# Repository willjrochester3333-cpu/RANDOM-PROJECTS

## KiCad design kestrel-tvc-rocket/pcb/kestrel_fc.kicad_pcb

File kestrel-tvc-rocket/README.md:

# KESTREL-2: a thrust-vector-controlled model rocket with four steerable fins

A reusable, 3D-printed, ~0.9 m model rocket that flies to about **157 m** on a TSP F35, **steers its motor**
(two-axis thrust vector control) and its
**four fin tabs** (roll, pitch and yaw; each tab's servo sits inside the thick bottom band of its fin and turns it
directly),
**stands up on its own four fins**, releases its parachute **at apogee**
with a servo latch under the nose cone (no pyrotechnics), carries a **payload of up to 50 g** behind a lockable
door, films the flight with a camera hidden inside it (looking out 30° down through a door with a lens port), logs
IMU, barometer and GPS data on a **custom flight-computer PCB** built around a Raspberry Pi Pico 2 W, and **sends
it all down live** over a licence-free 433 MHz telemetry radio (50 motion and 5 status frames a second) to
**Mission Control**, which flies the rocket on a 3D map as it happens and **predicts where it will land**. It
comes with its own launch pad. It is built to
**fly again and again**: the legs it stands and lands on are **replaceable** (one bolt each, and designed to be the
part that breaks after a hard landing, not the fin can), and a **battery hatch** with a gap-free door lets you swap
the LiPo and plug in USB between flights without taking anything apart. **No soldering
anywhere**: the PCB comes assembled from JLCPCB and everything else plugs, screws or glues together. Estimated
build cost **≈ £403–422** with the telemetry radio, ≈ £317 without it (motors extra).

**Simulated launch video** (ground camera, onboard camera, live telemetry bottom left, graphs below; every seed is a
different flight): [`kestrel2_flight_seed7.mp4`](sim/results/video/kestrel2_flight_seed7.mp4) (TSP F35, 4.9 m/s
wind, 20 g payload). Make another with `python3 sim/video/make_flight_video.py --seed N`.

**Mission Control** (the ground-station screen): a 3D map of the range with the rocket flying on it **live over the
radio**, the flight events as they happen (liftoff, burnout, apogee, parachute out, landed), telemetry, steering
dials and charts, the radio link's health, a **landing prediction** with a search ring and a position you can copy
to a phone map, and every flight saved for replay; after landing the full 500 Hz log comes in over USB and is merged
with the radio recording. Open [`ground/kestrel_mission_control.html`](ground/kestrel_mission_control.html) in Chrome
or Edge (one file, works offline); **Simulated live** shows a whole flight through a simulated radio link. See
[ground/README.md](ground/README.md).

| | |
|---|---|
| Parts | **3**: bottom (fin can + 4 replaceable legs + TVC module + camera behind its door + telemetry radio + flight computer + battery behind a hatch), middle (payload bay with door · wall · parachute bay · release latch at the top), nose cone |
| Length / diameter / fin span | 903 mm (929 mm standing on its fin feet) / 56.3 mm (Estes BT-70) / 159 mm |
| Lift-off mass | 952 g with a TSP F35 and 25 g of payload (861 g without motor) |
| Motors | 29 mm TSP **F35-0** (mission); 24 mm TSP **E20-0** for the first two flights, in a printed adapter sleeve (the D20 fits too, but is not in the flight programme) |
| Apogee (simulated, F35) | **157 m** nominal with 25 g of payload (164 m with an empty bay); Monte Carlo mean 166 m, 90 % of flights 135–200 m. E20: 41 m (about 47 m on the first flights, which carry no payload) |
| Stability | +0.72 to +0.84 calibres at lift-off (empty to full payload bay, with 51 g of nose ballast), +0.91 to +1.02 at burn-out: still flies straight enough to recover normally if all six steering servos fail |
| TVC | 2-axis gimbal for 29 mm motors, ±6° vector limit, 2 × MG90S, 500 Hz control loop |
| Fins | 4 × normal 4 mm fins with a half-round leading edge; only the bottom band (45 mm next to the tail) is 15 mm thick (17 mm round the servo), joined by a smooth 15° wedge, and holds the tab hinge, the tab servo (in a pocket open at the tip) and its lead channel; band and tabs taper to thin trailing edges below the tail |
| Multi-flight | **replaceable legs** (tough PLA, one M3 bolt onto a solid tongue under each fin tip; the post is the designed weak point at about 7.5 kg outward / 11.5 kg sideways at the foot, while the fin can holds about twice that); **battery hatch** on the rod side: the pack slides out and the Pico's USB socket is right there; the door sits on the tube and overlaps the opening by 2 mm all round |
| Fin tabs | 4 trailing-edge tabs, ±15°, each turned directly by an MG90S inside its fin (servo shaft = hinge line: no pods, pushrods or hinge pins); hold roll in boost and coast, share pitch/yaw with the TVC in the burn, steer alone in the coast |
| Recovery | 36 in parachute, spring ejection, servo-released snap-in latch, 5.2 m/s landing; from 157 m it drifts about 46 m for every 1 m/s of wind |
| Payload | 130 mm bay, 32 × 50 mm hinged door with a quarter-turn lock, 4 × M3 mounting holes, up to 50 g |
| Flight computer | Pico 2 W + LSM6DSO IMU + BMP580 baro + ATGM336H GPS + 16 MB log, 4-layer 40 × 82 mm PCB (v3), 7 servo ports, a radio socket |
| Telemetry | Holybro SiK V3 433 MHz pair, set to 8 dBm (≈ 6 mW e.r.p., inside the UK's 10 mW limit) and kept under the 10 %-an-hour airtime rule by the firmware; MAVLink-framed binary frames with a CRC, 50 motion + 5 status a second in flight, 1.5 a second on the pad. Nothing sent from the ground changes the flight: the rocket only notes the ground station's heartbeat |
| Camera | SQ12-class 23 mm cube **inside** the bottom tube, in a cradle behind a door with a lens port and a low brow, looking out 30° down (the old external pod is gone: −71 % camera drag) |
| Launch pad | printed hub, 3 dowel legs, 1 m (or 1.5 m) × 6 mm rod, 0–15° tilt, 200 mm tile the rocket stands on |

## How it was verified

- **Simulation with the real flight code in the loop.** A 6-DOF simulator, checked against RocketPy (every
  quantity within 0.3 %), flies the actual C++ flight software 500 times a second, including the fin-tab mixer.
  **Scenario and fault suite: 44 of 44 graded cases pass** (plus 3 informational cases).
  **1500-flight Monte Carlo** (1000 on the F35, 400 on the E20, 100 on the D20): **1500 of 1500** meet every
  normal-flight criterion. A **first-flight study** of the E20 (700 flights: flight 1 with the fin tabs off, flight
  2 with them on, and 100 in more wind than allowed): 700 of 700, the canopy fully open at about 40 m. A stress Monte
  Carlo with about twice the error spreads and wind up to 9 m/s: 99.7 % meet every normal-flight criterion and
  99.9 % recover safely; a tab-effectiveness Monte Carlo: 200 of 200. About 3,700 simulated flights on the final design.
  → [docs/SIMULATION_REPORT.md](docs/SIMULATION_REPORT.md)
- **CAD checked automatically on every run.** All 40 printed parts are watertight, single-body and fit a
  220 × 220 × 250 mm bed, and an overhang check confirms they print as exported without support material (three
  marked parts excepted). Exact-geometry interference checks cover 2485 part pairs, plus sweeps of every mechanism
  through its full travel: the gimbal in 24 directions at 7° (with the F35 and with the 24 mm adapter, against the
  frame, servos, horns and pushrods), all four tabs at ±17°, the payload door through 0–100° and the release latch.
  All come back clean. Masses and positions feed the simulator, the av-bay is
  generated from the PCB's KiCad layout, and every number the firmware and simulator take from `design.json`
  (linkage ratios, tab geometry, leg geometry, IMU position, the camera door's brow) is checked against the CAD. The
  strength of every section of the fin, leg and tongue is computed from slices of the real CAD solid.
- **PCB** (v3, with the radio socket): schematic checked pin-for-pin against the circuit source, DRC 0
  violations, all 65 nets routed, gerbers re-read by an independent viewer. → [docs/PCB.md](docs/PCB.md)
- **Firmware** (v3.00): 375,585 flight-core checks (including the radio frames against pymavlink's reference
  frames and an hour stuck at full rate against the airtime limit), 148 firmware-logic checks, a 0-warning
  cross-compile and a ready-to-flash UF2. → [docs/FIRMWARE.md](docs/FIRMWARE.md)
- **Mission Control**: its radio decoder is tested against pymavlink frames and against a second, independent
  decoder in Python, including a damaged link; the whole page was run in a headless browser through a simulated
  flight (55 frames a second, no errors).

Honest gaps against what we agreed:

- **Apogee**: you asked for 200 m. On the 29 mm TSP F35 the rocket reached 188 m; making it a multiple-flight
  rocket added 48 g (170 m), and the telemetry radio, its antenna and cradles and 5 g more nose ballast to keep the
  same stability added another 48 g, so it now reaches **157 m** with 25 g of payload (164 m with an empty bay).
  Hiding the camera inside cut its drag by 71 % and won back a little of that. The TVC module takes 29 mm motors;
  the E20 flies in a printed adapter for the first two flights. The price of height is drift: about 30 s under the
  parachute, so it needs a recovery area of about 500 m downwind in winds up to 6 m/s, or 250 m if you fly it only
  in 3 m/s or less. The details, with what-if numbers, are in the simulation report, section 3.
- **Budget**: ≈ £317 without the radio against the ~£270 we aimed for (four extra servos, the larger 36 in
  parachute, the ejection spring that only comes in a pack of 10, the servos-in-the-fins design and the multi-flight
  parts); the radio adds ≈ £86–105. Two radio items (the antenna and the antenna extension) were not price-checked.
  → [docs/BOM.md](docs/BOM.md)
- **Not checked on real hardware yet**: the radio's range inside the rocket (its antenna stands inside the
  airframe, next to the wiring), and the masses of the radio parts (estimates). The test plan has a bench and a
  field range test before the first flight.

**Where the project stands, in one page:** [docs/STATUS.md](docs/STATUS.md).

Real flights then confirm what models cannot; [docs/TEST_PLAN.md](docs/TEST_PLAN.md) takes you from the bench to
the first F35 flight in steps (two E20 flights first: TVC only, then with the fin tabs).

## Build it

1. **Order the PCB** (1–3 weeks): [docs/PCB.md → Ordering from JLCPCB](docs/PCB.md#ordering-from-jlcpcb)
2. **Buy the rest**: [docs/BOM.md](docs/BOM.md)
3. **Print and assemble**: [docs/BUILD_GUIDE.md](docs/BUILD_GUIDE.md)
4. **Flash and set up**: drag `firmware/pico/kestrel_fc.uf2` onto the Pico, then `calaxes`, `dirtest`, `tabtest`,
   `tvctest`, `fintest`
5. **Test**: [docs/TEST_PLAN.md](docs/TEST_PLAN.md) → **fly**: [docs/PREFLIGHT_CHECKLIST.md](docs/PREFLIGHT_CHECKLIST.md)
6. **Read first**: [docs/SAFETY_AND_LEGAL.md](docs/SAFETY_AND_LEGAL.md) (UKRA/BMFA, CAA, motors, LiPo, wind limits)

## What's where

Every file is listed and explained in [FILES.md](FILES.md).

```
design.json              master parameters: airframe, fins + tabs, TVC, payload, recovery, every component's mass/position
cad/                     Blender + manifold3d parametric model
  kestrel_cad.py           blender -b -P cad/kestrel_cad.py -- [--no-render] [--fast] [--view=NAME]
  kestrel.blend            scene 1: complete rocket + the same rocket cut open + every part laid out with its name;
                           scenes 2-7: exploded view, cut-aways, door open, tabs deflected, fin cut open, on the launch pad
  kestrel_rocket.blend     just the constructed rocket, every part in place; hide "Body tubes" to look inside
  kestrel_tvc_module.blend the TVC module on its own (its two servo leads come out of the top) + assembly steps
  kestrel_parachute_open.blend  the rocket descending under its open parachute
  stl/                     40 print-ready STLs + check_report.md (3 of them: the 24 mm motor adapter set)
  renders/                 the images above
  interference_report.md   part pairs and mechanism sweeps
pcb/                     KiCad 7 project, circuit-as-code, autorouter, production files for JLCPCB
  kestrel_fc.kicad_pro/.kicad_sch/.kicad_pcb, kestrel_fc_schematic.pdf
  production/              gerbers zip, BOM + pick-and-place CSVs, assembly drawing
firmware/
  core/                    flight core (estimation, TVC, fin-tab mixer, state machine) + unit tests
  pico/                    Pico 2 W application, drivers, host tests; kestrel_fc.uf2 = ready to flash
  sil/                     simulator bridge (software-in-the-loop)
  tools/                   kestrel_link.py (USB shell, log download, plots, radio recorder), gen_motor_db.py
sim/                     6-DOF simulator, scenarios, Monte Carlo, first-flight study, RocketPy validation, results/
  run_all.sh               every simulation suite in order (about 45 min on 4 cores)
  video/                   launch-video pipeline (simulation → Blender → telemetry + graphs → MP4)
docs/                    shopping list, build guide, PCB, firmware, test plan, checklist, safety, simulation report
ground/                  Mission Control: kestrel_mission_control.html = live radio, 3D map, landing prediction, replay (offline)
  radio_frames.py, test_radio.mjs   the radio frame format in Python + the page decoder's tests
```

## Change it

Everything is parametric and connected: edit `design.json` (or the PCB layout in `pcb/circuit.py`), then
re-run the chain. The CAD script stops with a message if `design.json` and the CAD/PCB disagree.

```bash
blender -b -P cad/kestrel_cad.py -- --no-render && python3 cad/check_parts.py && python3 cad/mass_properties.py
```

```bash
python3 firmware/tools/gen_motor_db.py && cmake --build firmware/build-host && (cd firmware/build-host && ctest)
```

```bash
sh sim/run_all.sh
```

Tools: Blender 4.0, KiCad 7, Python 3 (numpy, matplotlib, pillow, trimesh, manifold3d, rocketpy), ffmpeg,
Raspberry Pi Pico SDK 2.1, arm-none-eabi-gcc.

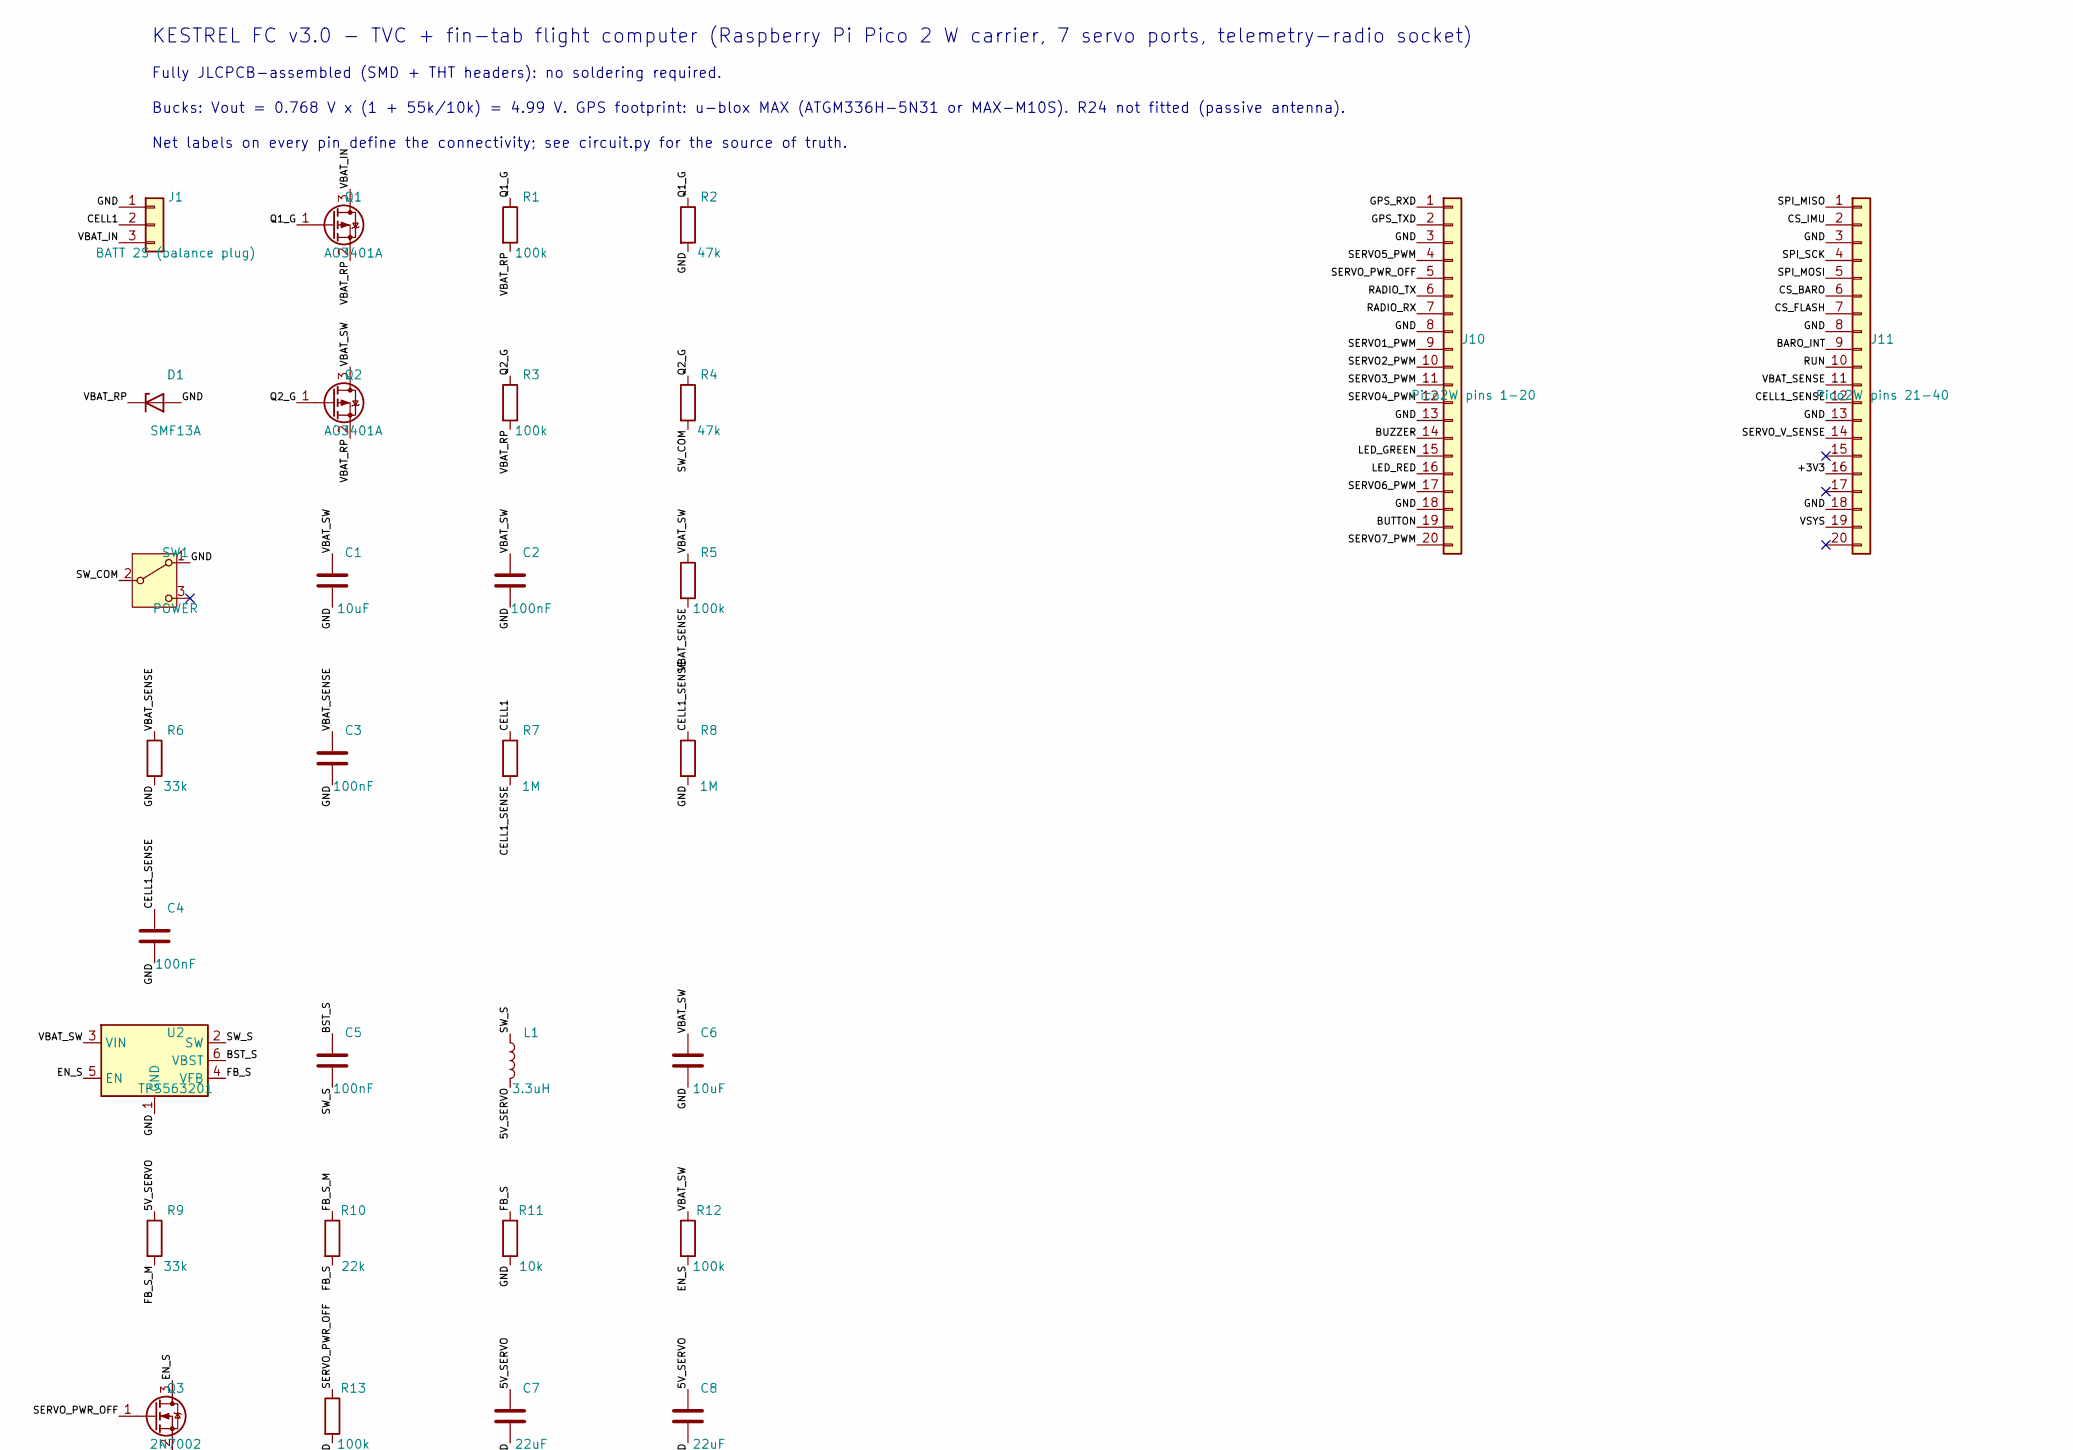
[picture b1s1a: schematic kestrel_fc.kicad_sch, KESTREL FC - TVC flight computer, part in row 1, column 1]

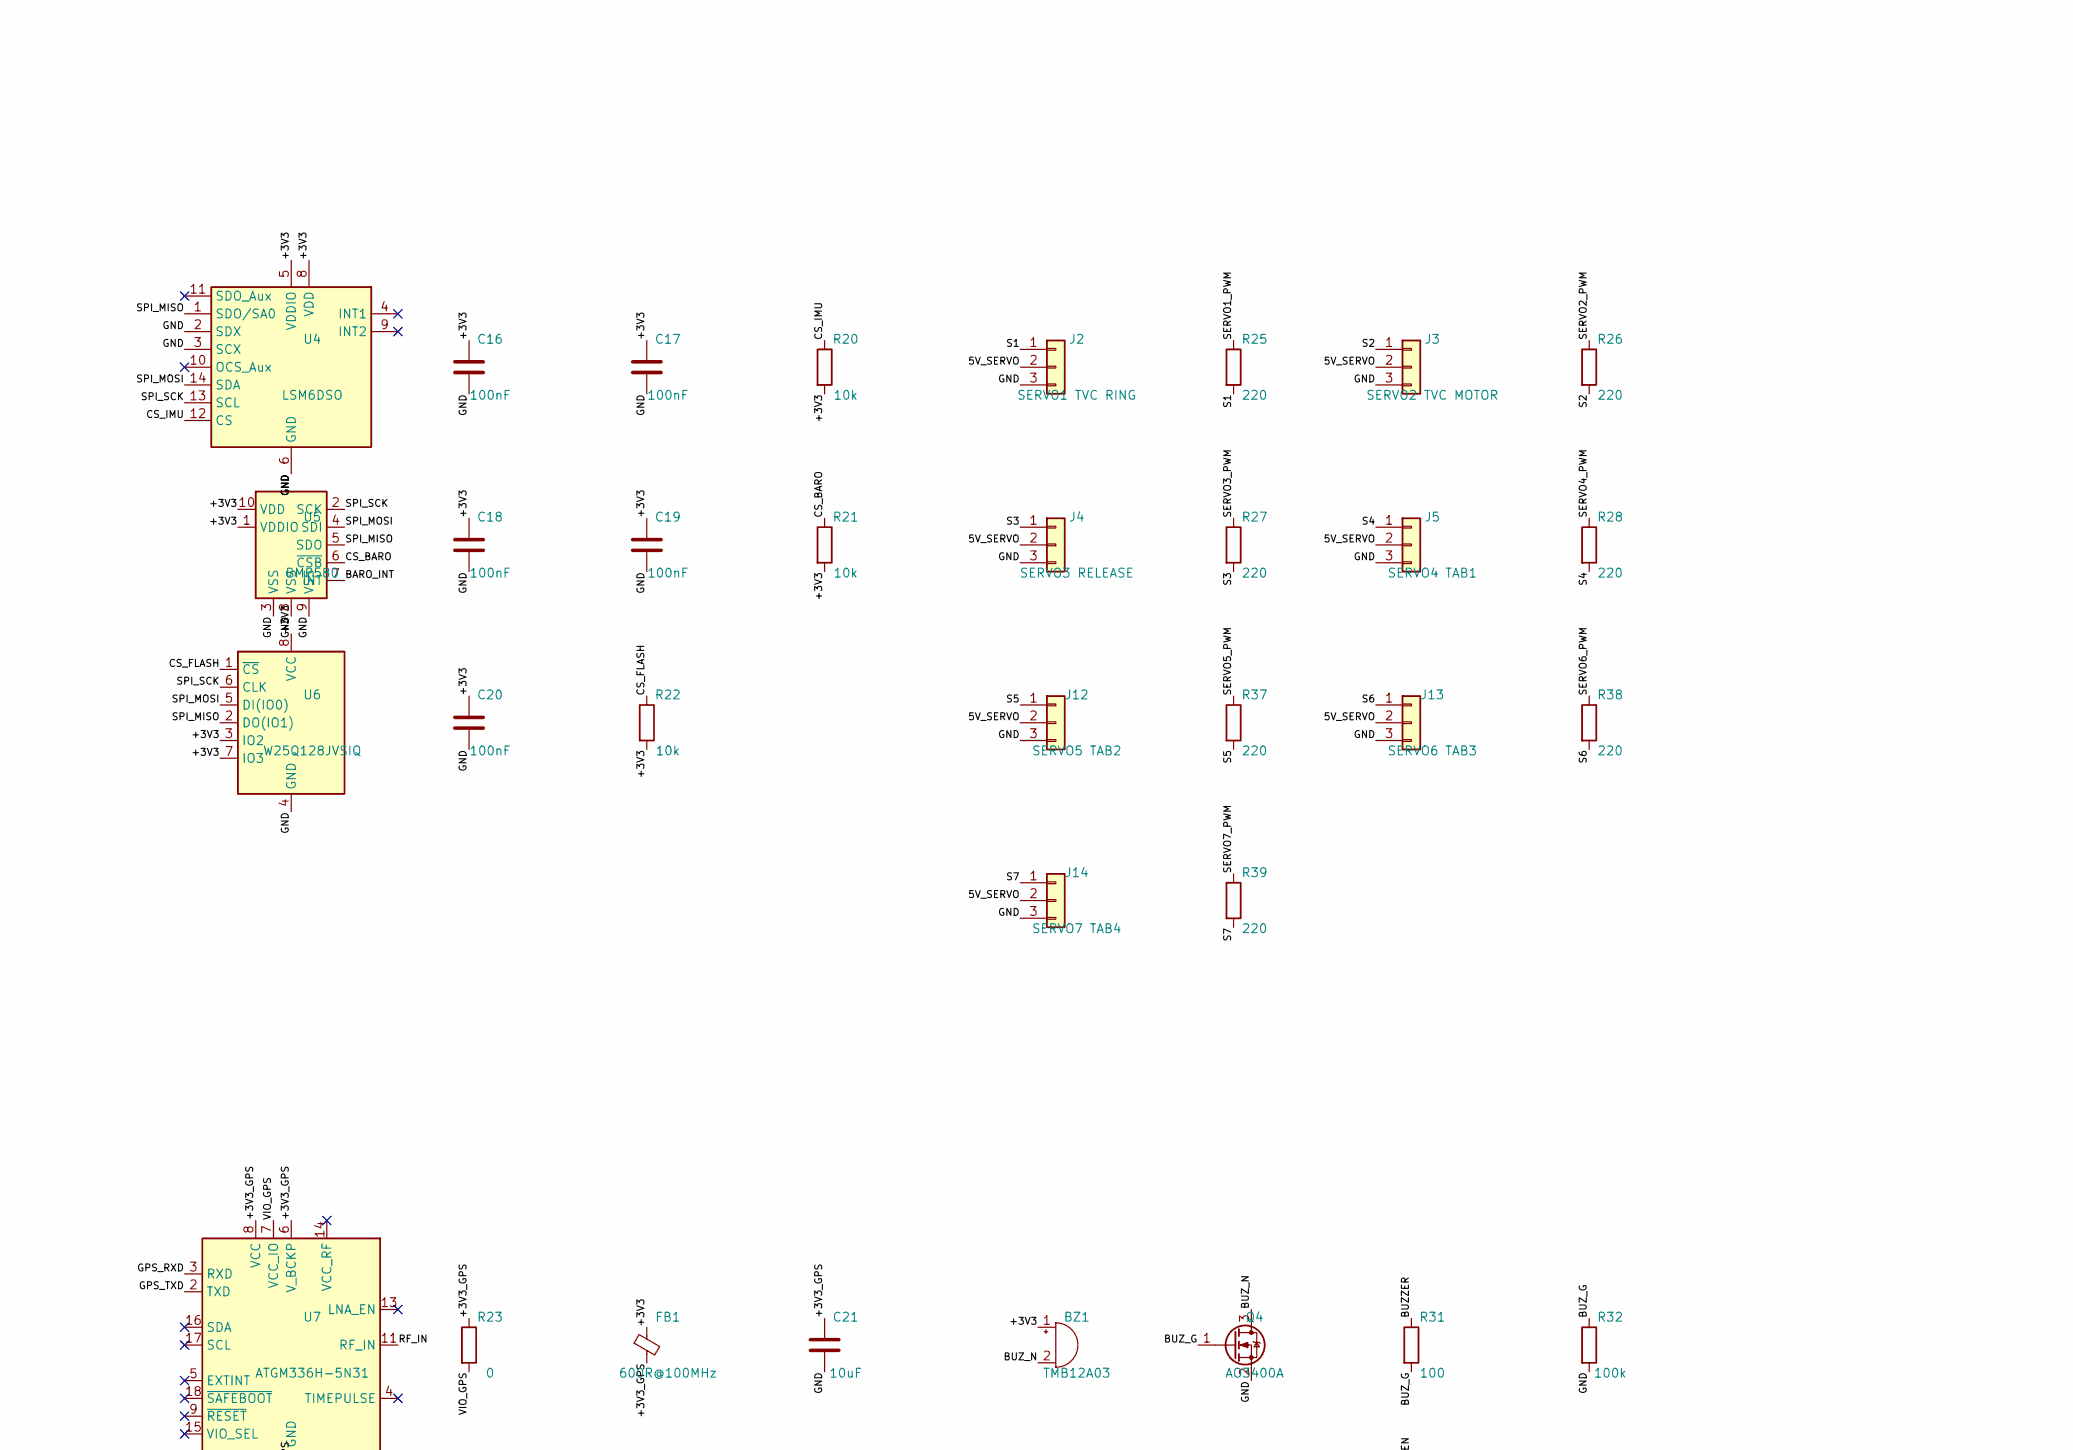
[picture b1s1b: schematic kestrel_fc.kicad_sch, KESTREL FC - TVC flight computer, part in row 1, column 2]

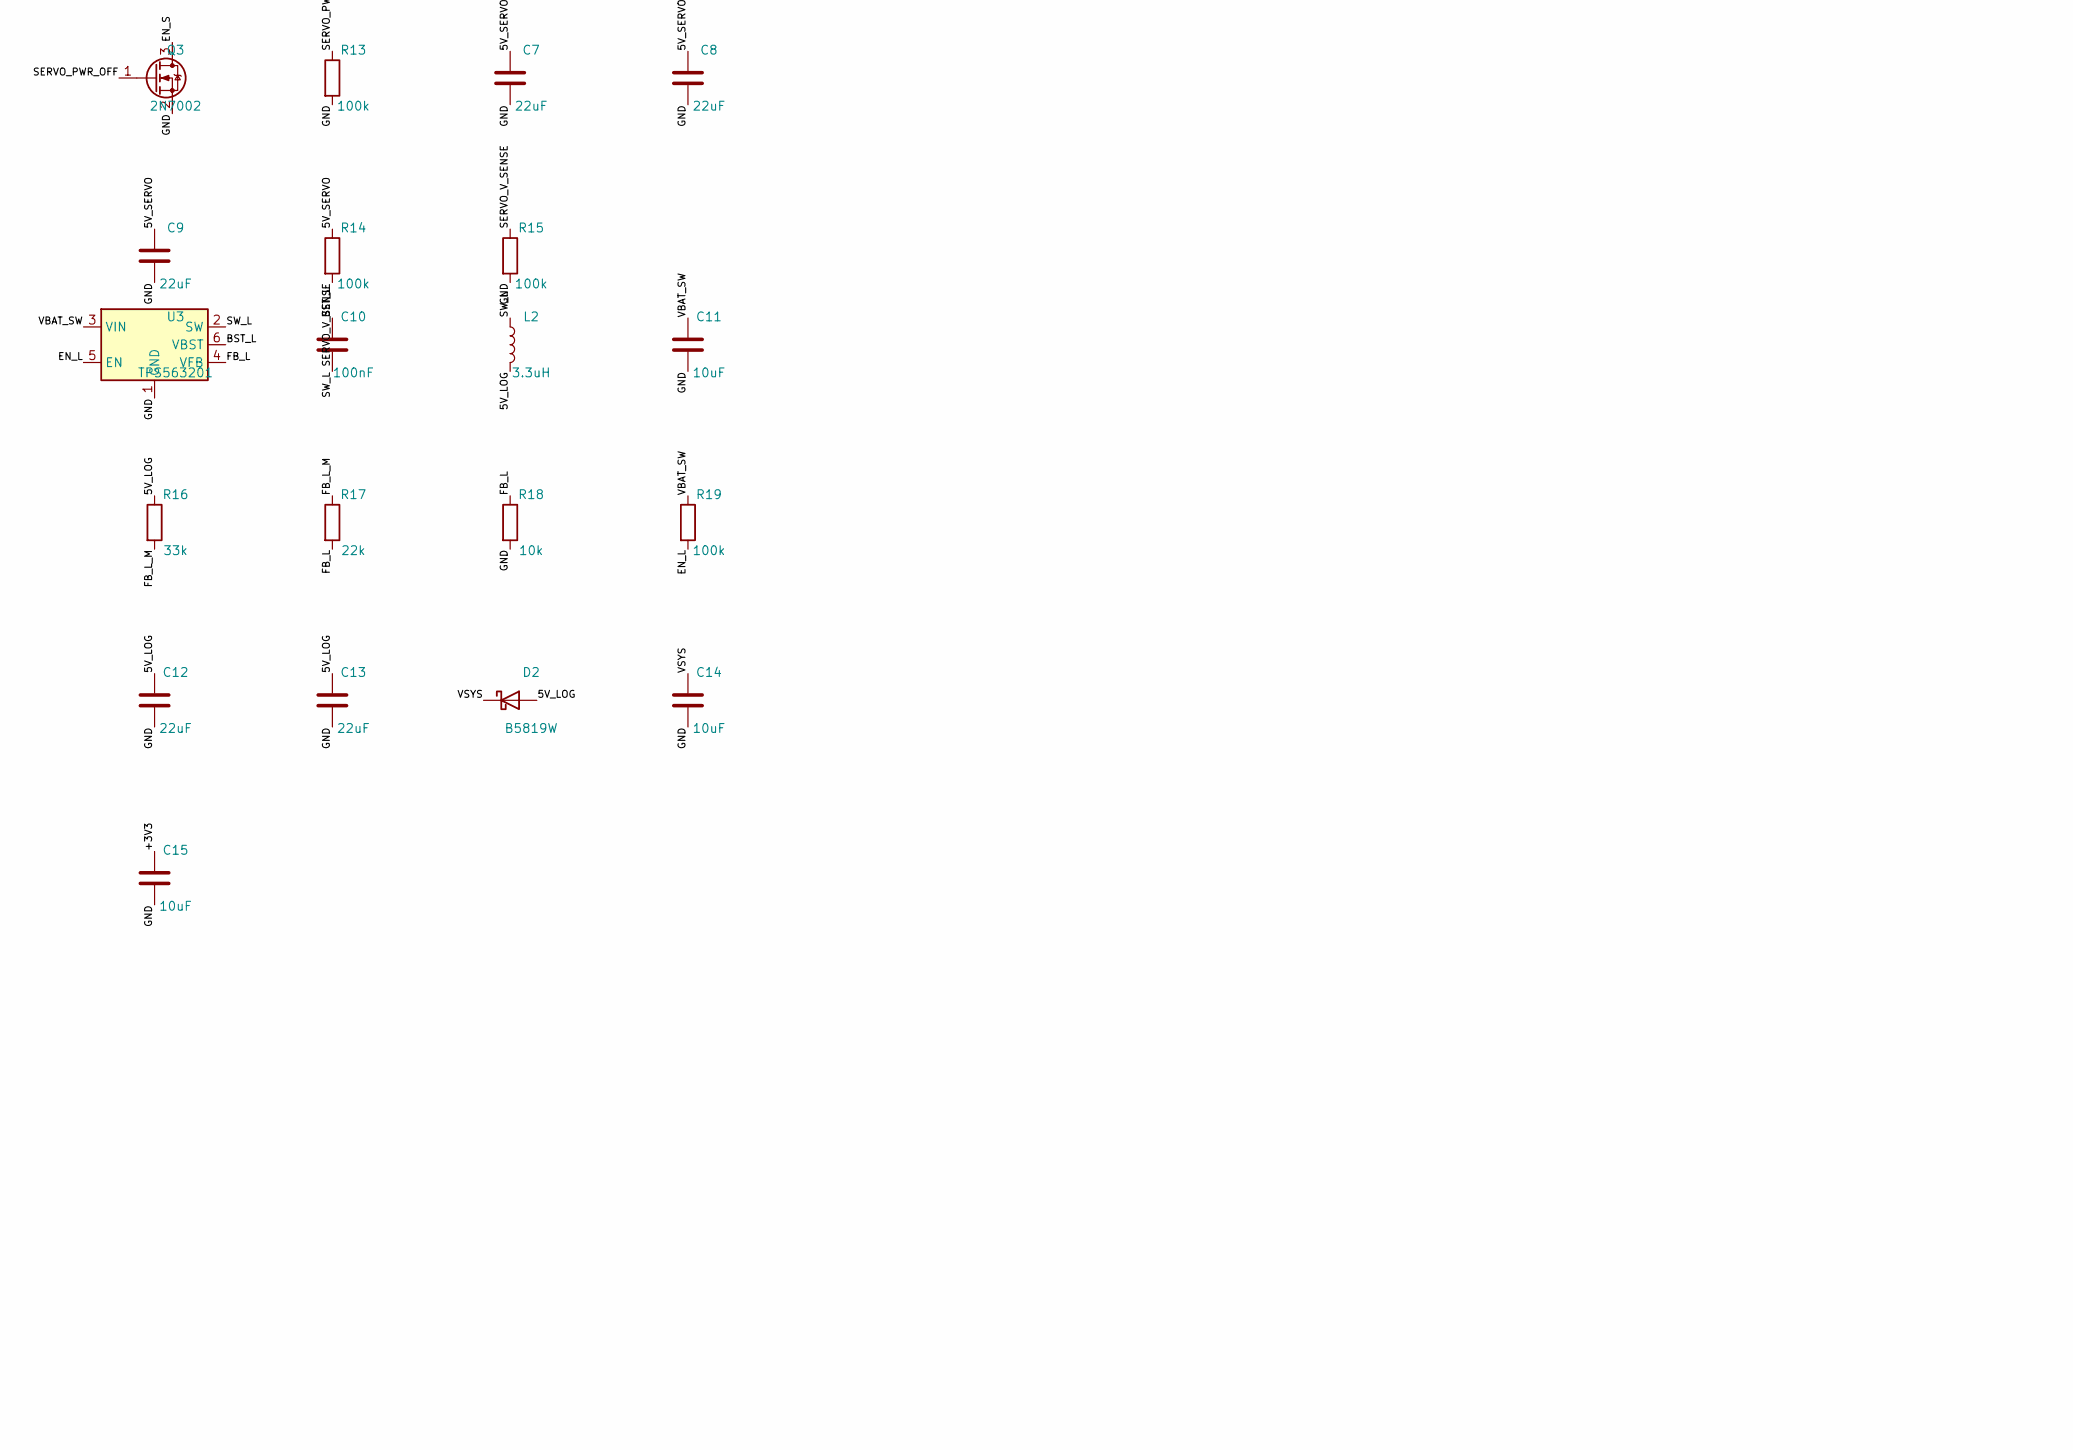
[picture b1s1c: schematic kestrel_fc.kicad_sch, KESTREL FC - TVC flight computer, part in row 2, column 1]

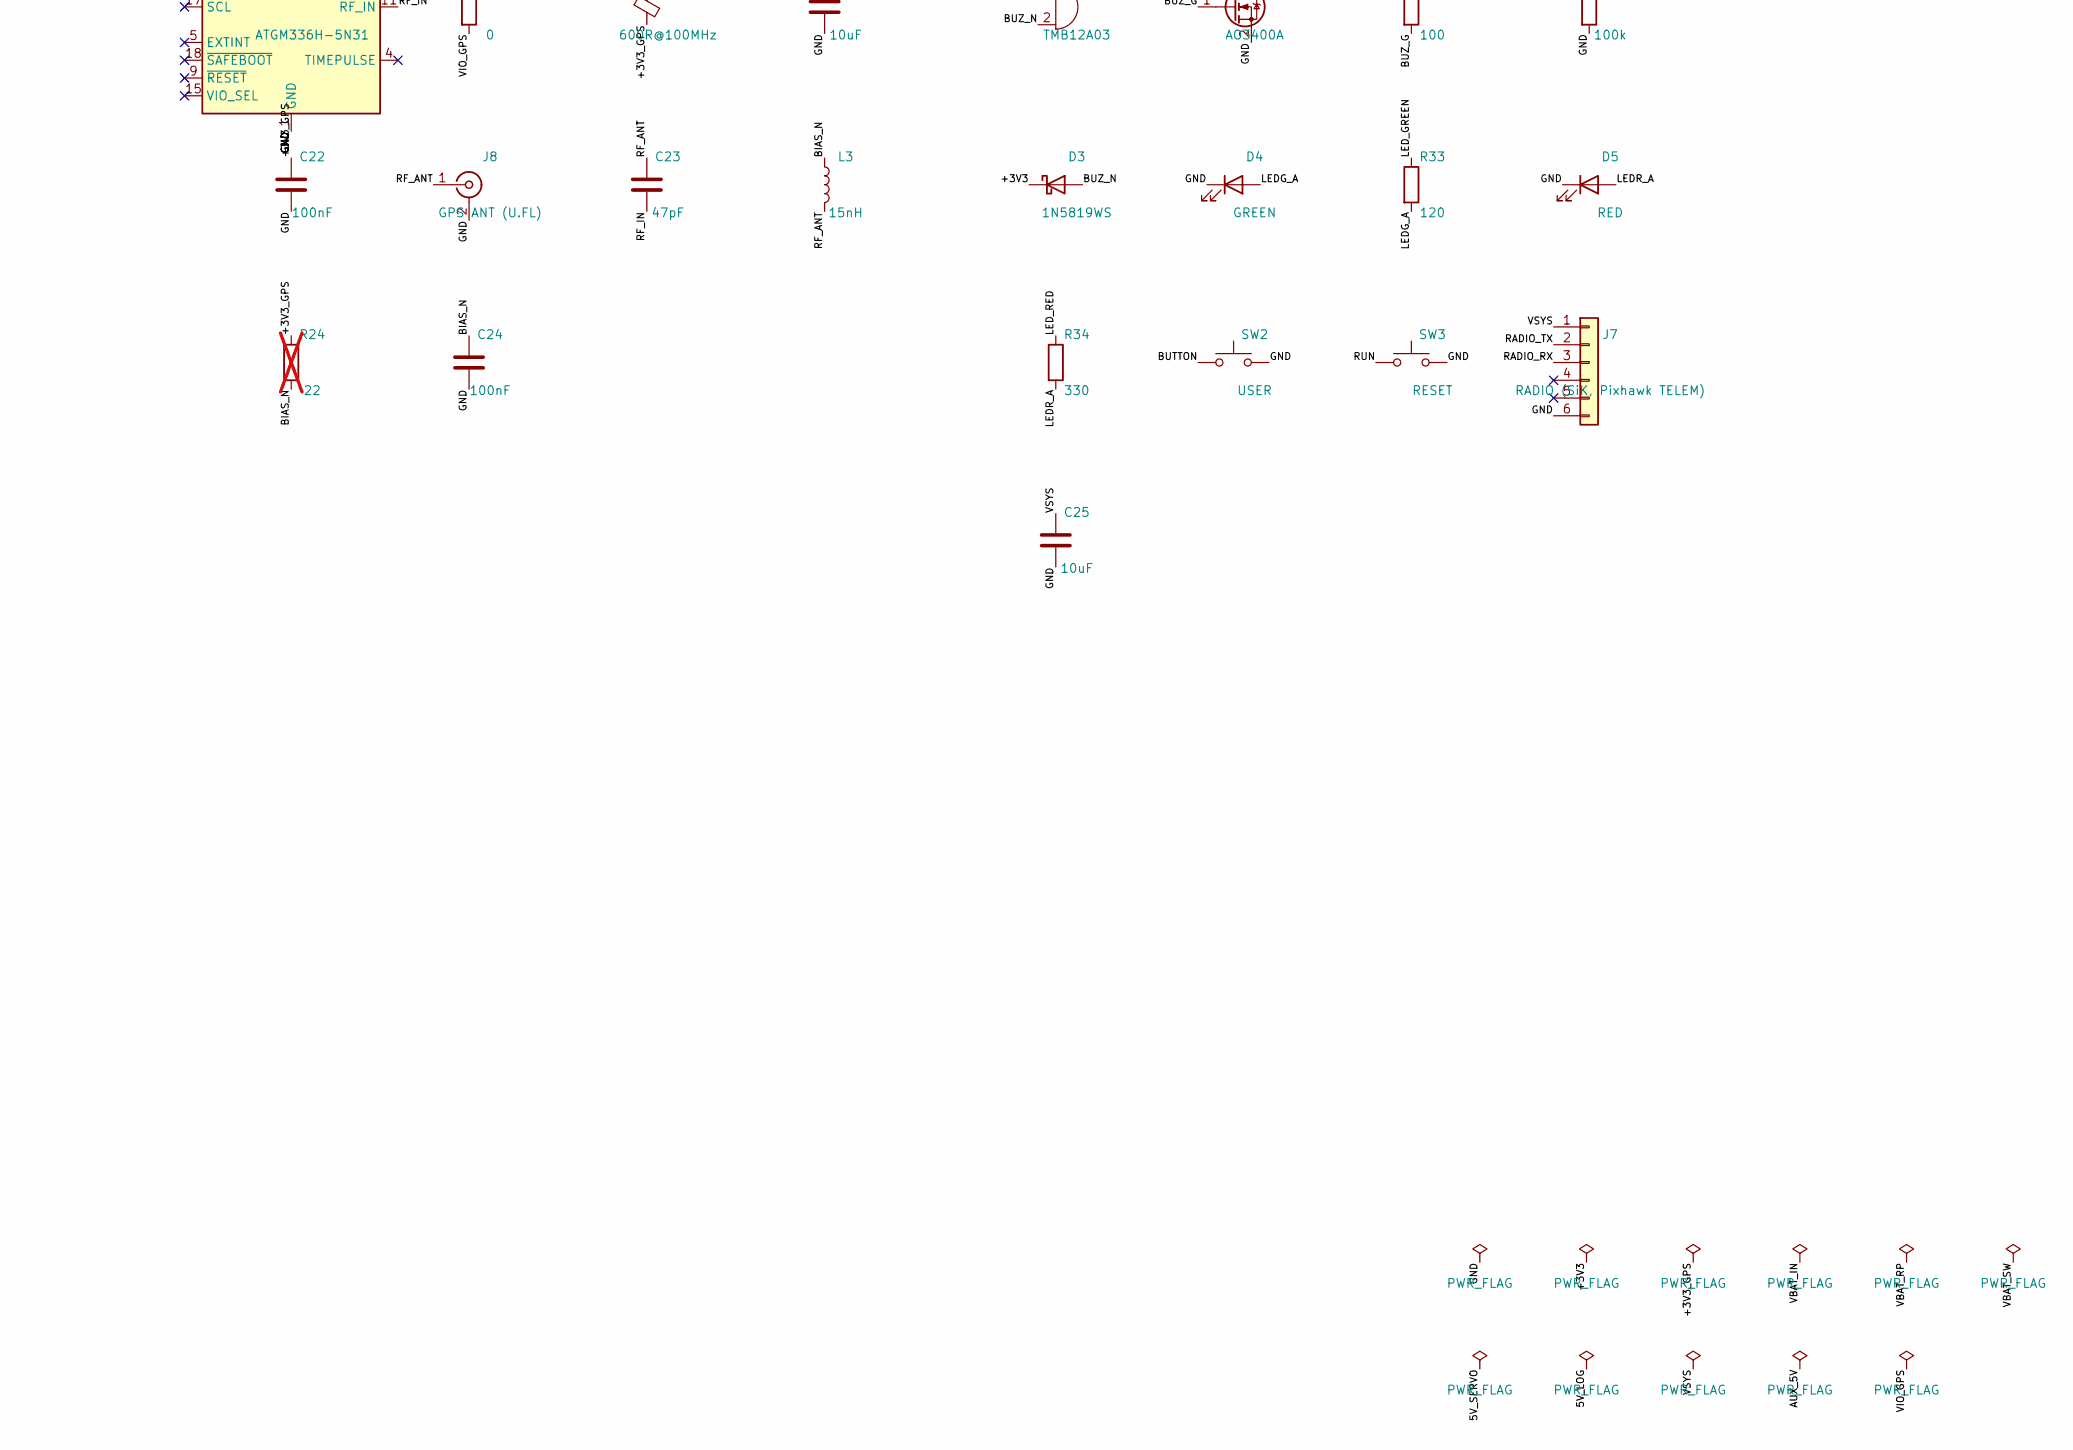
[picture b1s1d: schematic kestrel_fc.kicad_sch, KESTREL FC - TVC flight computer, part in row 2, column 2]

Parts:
BZ1: TMB12A03; Buzzer_12x9.5RM7.6; MPN 12 mm active buzzer 3V 85 dB; LCSC C96222
C1, C6, C11, C14, C15, C21, C25: 10uF; C_0805_2012Metric; MPN SMD:C 10uF; LCSC C15850
C2, C3, C4, C5, C10, C16, C17, C18, C19, C20, C22, C24: 100nF; C_0402_1005Metric; MPN SMD:C 100nF; LCSC C1525
C7, C8, C9, C12, C13: 22uF; C_1206_3216Metric; MPN SMD:C 22uF; LCSC C12891
C23: 47pF; C_0402_1005Metric; MPN SMD:C 47pF; LCSC C1567
D1: SMF13A; D_SOD-123F; MPN SMF13A TVS 13V; LCSC C41376087
D2: B5819W; D_SOD-123; MPN B5819W SL; LCSC C8598
D3: 1N5819WS; D_SOD-323; MPN flyback; LCSC C191023
D4: GREEN; LED_0805_2012Metric; MPN 0805 green; LCSC C2297
D5: RED; LED_0805_2012Metric; MPN 0805 red; LCSC C84256
FB1: 600R@100MHz; L_0805_2012Metric; MPN 0805 ferrite 600R 500mA; LCSC C1017
J1: BATT 2S (balance plug); JST_XH_B3B-XH-A_1x03_P2.50mm_Vertical; MPN JST B3B-XH-A; LCSC C144394
J2: SERVO1 TVC RING; PinHeader_1x03_P2.54mm_Vertical; MPN Male header 1x3 2.54 mm; LCSC C49257
J3: SERVO2 TVC MOTOR; PinHeader_1x03_P2.54mm_Vertical; MPN Male header 1x3 2.54 mm; LCSC C49257
J4: SERVO3 RELEASE; PinHeader_1x03_P2.54mm_Vertical; MPN Male header 1x3 2.54 mm; LCSC C49257
J5: SERVO4 TAB1; PinHeader_1x03_P2.54mm_Vertical; MPN Male header 1x3 2.54 mm; LCSC C49257
J7: RADIO (SiK, Pixhawk TELEM); JST_GH_BM06B-GHS-TBT_1x06-1MP_P1.25mm_Vertical; MPN JST BM06B-GHS-TBT(LF)(SN); LCSC C189892
J8: GPS ANT (U.FL); U.FL_Hirose_U.FL-R-SMT-1_Vertical; MPN Hirose U.FL-R-SMT-1(80); LCSC C88374
J10: Pico2W pins 1-20; PinSocket_1x20_P2.54mm_Vertical; MPN Female header 1x20 2.54 mm H8.5; LCSC C7499336
J11: Pico2W pins 21-40; PinSocket_1x20_P2.54mm_Vertical; MPN Female header 1x20 2.54 mm H8.5; LCSC C7499336
J12: SERVO5 TAB2; PinHeader_1x03_P2.54mm_Vertical; MPN Male header 1x3 2.54 mm; LCSC C49257
J13: SERVO6 TAB3; PinHeader_1x03_P2.54mm_Vertical; MPN Male header 1x3 2.54 mm; LCSC C49257
J14: SERVO7 TAB4; PinHeader_1x03_P2.54mm_Vertical; MPN Male header 1x3 2.54 mm; LCSC C49257
L1, L2: 3.3uH; L_Sunlord_MWSA0503S; MPN Sunlord MWSA0503S-3R3MT 5.5A; LCSC C408409
L3: 15nH; L_0402_1005Metric; MPN 0402 15nH (antenna DC feed); LCSC C27143
Q1, Q2: AO3401A; SOT-23; MPN AO3401A; LCSC C15127
Q3: 2N7002; SOT-23; MPN 2N7002; LCSC C8545
Q4: AO3400A; SOT-23; MPN AO3400A; LCSC C20917
R1, R3, R5, R12, R13, R14, R15, R19, R32: 100k; R_0402_1005Metric; MPN 0402 100k 1%; LCSC C25741
R2, R4: 47k; R_0402_1005Metric; MPN 0402 47k 1%; LCSC C25792
R6, R9, R16: 33k; R_0402_1005Metric; MPN 0402 33k 1%; LCSC C25779
R7, R8: 1M; R_0402_1005Metric; MPN 0402 1M 1%; LCSC C26083
R10, R17: 22k; R_0402_1005Metric; MPN 0402 22k 1%; LCSC C25768
R11, R18, R20, R21, R22: 10k; R_0402_1005Metric; MPN 0402 10k 1%; LCSC C25744
R23: 0; R_0402_1005Metric; MPN 0402 0 1%; LCSC C17168
R24: 22; R_0402_1005Metric; MPN 0402 22 1%; LCSC C25092; not fitted
R25, R26, R27, R28, R37, R38, R39: 220; R_0402_1005Metric; MPN 0402 220 1%; LCSC C25091
R31: 100; R_0402_1005Metric; MPN 0402 100 1%; LCSC C25076
R33: 120; R_0402_1005Metric; MPN 0402 120 1%; LCSC C25079
R34: 330; R_0402_1005Metric; MPN 0402 330 1%; LCSC C25104
SW1: POWER; SW_SPDT_PCM12; MPN C&K PCM12SMTR; LCSC C221841
SW2: USER; SW_Push_1P1T_XKB_TS-1187A; MPN XKB TS-1187A 5.1 mm; LCSC C318884
SW3: RESET; SW_Push_1P1T_XKB_TS-1187A; MPN XKB TS-1187A 5.1 mm; LCSC C318884
U2, U3: TPS563201; TSOT-23-6; MPN TI TPS563201DDCR; LCSC C116592
U4: LSM6DSO; LGA-14_3x2.5mm_P0.5mm_LayoutBorder3x4y; MPN ST LSM6DSOTR (alt: LSM6DS3TR-C C967633); LCSC C2655100
U5: BMP580; Bosch_LGA-10_2x2mm_P0.5mm_BMP58x; MPN Bosch BMP580; LCSC C22391138
U6: W25Q128JVSIQ; SOIC-8_5.23x5.23mm_P1.27mm; MPN Winbond W25Q128JVSIQ 16 MB; LCSC C97521
U7: ATGM336H-5N31; ublox_MAX; MPN ZHONGKEWEI ATGM336H-5N31 (alt: u-blox M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; LCSC C90770

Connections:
5V_LOG: C12.1, C13.1, D2.2 (A), L2.2, R16.1
5V_SERVO: C7.1, C8.1, C9.1, J2.2, J3.2, J4.2, J5.2, J12.2, J13.2, J14.2, L1.2, R9.1, R14.1
+3V3: BZ1.1 (+), C15.1, C16.1, C17.1, C18.1, C19.1, C20.1, D3.1 (K), FB1.1, J11.16, R20.2, R21.2, R22.2, U4.5 (VDDIO), U4.8 (VDD), U5.1 (VDDIO), U5.10 (VDD), U6.3 (IO2), U6.7 (IO3), U6.8 (VCC)
+3V3_GPS: C21.1, C22.1, FB1.2, R23.1, R24.1, U7.6 (V_BCKP), U7.8 (VCC)
BARO_INT: J11.9, U5.7 (INT)
BIAS_N: C24.1, L3.1, R24.2
BST_L: C10.1, U3.6 (VBST)
BST_S: C5.1, U2.6 (VBST)
BUTTON: J10.19, SW2.1
BUZZER: J10.14, R31.1
BUZ_G: Q4.1 (G), R31.2, R32.1
BUZ_N: BZ1.2 (-), D3.2 (A), Q4.3 (D)
CELL1: J1.2, R7.1
CELL1_SENSE: C4.1, J11.12, R7.2, R8.1
CS_BARO: J11.6, R21.1, U5.6 (~CSB)
CS_FLASH: J11.7, R22.1, U6.1 (~CS)
CS_IMU: J11.2, R20.1, U4.12 (CS)
EN_L: R19.2, U3.5 (EN)
EN_S: Q3.3 (D), R12.2, U2.5 (EN)
FB_L: R17.2, R18.1, U3.4 (VFB)
FB_L_M: R16.2, R17.1
FB_S: R10.2, R11.1, U2.4 (VFB)
FB_S_M: R9.2, R10.1
GND: C1.2, C2.2, C3.2, C4.2, C6.2, C7.2, C8.2, C9.2, C11.2, C12.2, C13.2, C14.2, C15.2, C16.2, C17.2, C18.2, C19.2, C20.2, C21.2, C22.2, C24.2, C25.2, D1.2 (A), D4.1 (K), D5.1 (K), J1.1, J2.3, J3.3, J4.3, J5.3, J7.6, J7.MP, J8.2 (Ext), J10.3, J10.8, J10.13, J10.18, J11.3, J11.8, J11.13, J11.18, J12.3, J13.3, J14.3, Q3.2 (S), Q4.2 (S), R2.2, R6.2, R8.2, R11.2, R13.2, R15.2, R18.2, R32.2, SW1.1 (A), SW2.2, SW3.2, U2.1 (GND), U3.1 (GND), U4.2 (SDX), U4.3 (SCX), U4.6 (GND), U4.7 (GND), U5.3 (VSS), U5.8 (VSS), U5.9 (VSS), U6.4 (GND), U7.1 (GND), U7.10 (GND), U7.12 (GND)
GPS_RXD: J10.1, U7.3 (RXD)
GPS_TXD: J10.2, U7.2 (TXD)
LEDG_A: D4.2 (A), R33.2
LEDR_A: D5.2 (A), R34.2
LED_GREEN: J10.15, R33.1
LED_RED: J10.16, R34.1
Q1_G: Q1.1 (G), R1.1, R2.1
Q2_G: Q2.1 (G), R3.1, R4.1
RADIO_RX: J7.3, J10.7
RADIO_TX: J7.2, J10.6
RF_ANT: C23.1, J8.1 (In), L3.2
RF_IN: C23.2, U7.11 (RF_IN)
RUN: J11.10, SW3.1
S1: J2.1, R25.2
S2: J3.1, R26.2
S3: J4.1, R27.2
S4: J5.1, R28.2
S5: J12.1, R37.2
S6: J13.1, R38.2
S7: J14.1, R39.2
SERVO1_PWM: J10.9, R25.1
SERVO2_PWM: J10.10, R26.1
SERVO3_PWM: J10.11, R27.1
SERVO4_PWM: J10.12, R28.1
SERVO5_PWM: J10.4, R37.1
SERVO6_PWM: J10.17, R38.1
SERVO7_PWM: J10.20, R39.1
SERVO_PWR_OFF: J10.5, Q3.1 (G), R13.1
SERVO_V_SENSE: J11.14, R14.2, R15.1
SPI_MISO: J11.1, U4.1 (SDO/SA0), U5.5 (SDO), U6.2 (DO(IO1))
SPI_MOSI: J11.5, U4.14 (SDA), U5.4 (SDI), U6.5 (DI(IO0))
SPI_SCK: J11.4, U4.13 (SCL), U5.2 (SCK), U6.6 (CLK)
SW_COM: R4.2, SW1.2 (B)
SW_L: C10.2, L2.1, U3.2 (SW)
SW_S: C5.2, L1.1, U2.2 (SW)
VBAT_IN: J1.3, Q1.3 (D)
VBAT_RP: D1.1 (K), Q1.2 (S), Q2.2 (S), R1.2, R3.2
VBAT_SENSE: C3.1, J11.11, R5.2, R6.1
VBAT_SW: C1.1, C2.1, C6.1, C11.1, Q2.3 (D), R5.1, R12.1, R19.1, U2.3 (VIN), U3.3 (VIN)
VIO_GPS: R23.2, U7.7 (VCC_IO)
VSYS: C14.1, C25.1, D2.1 (K), J7.1, J11.19

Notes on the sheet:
KESTREL FC v3.0 - TVC + fin-tab flight computer (Raspberry Pi Pico 2 W carrier, 7 servo ports, telemetry-radio socket)
Fully JLCPCB-assembled (SMD + THT headers): no soldering required.
Bucks: Vout = 0.768 V x (1 + 55k/10k) = 4.99 V. GPS footprint: u-blox MAX (ATGM336H-5N31 or MAX-M10S). R24 not fitted (passive antenna).
Net labels on every pin define the connectivity; see circuit.py for the source of truth.

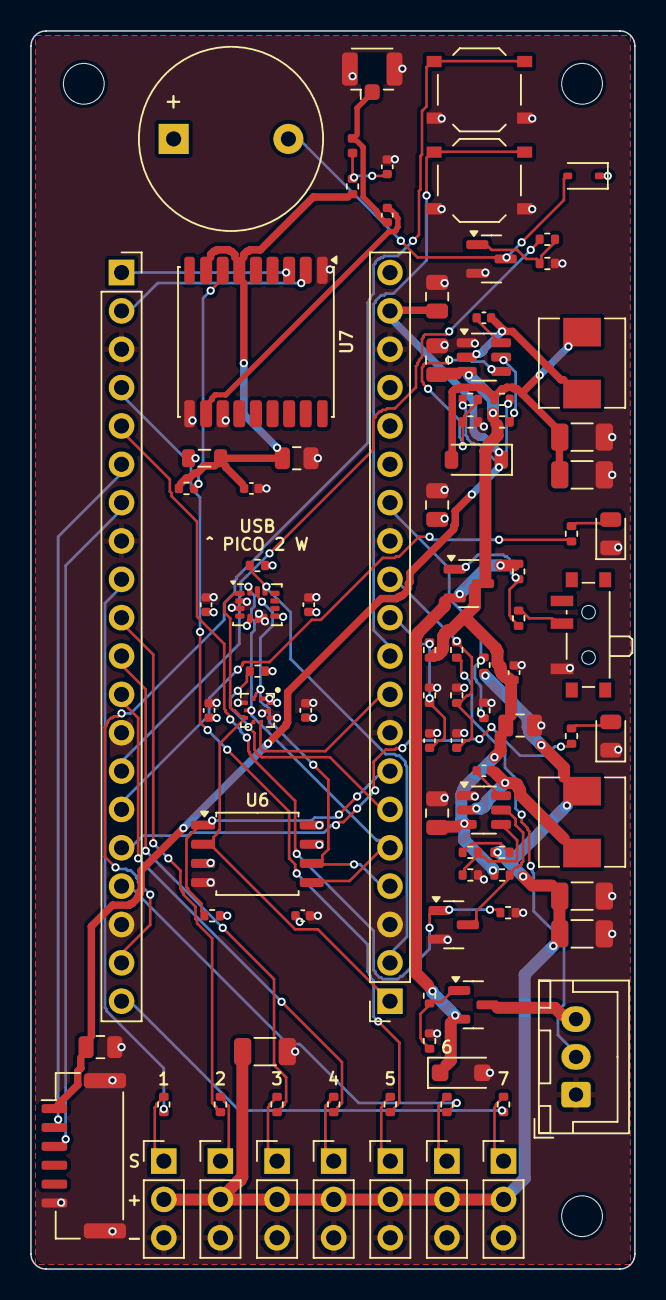
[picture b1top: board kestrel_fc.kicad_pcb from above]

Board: 4 copper layers, 40.0 x 82.0 mm, 98 parts (0 on the bottom side), 65 nets.

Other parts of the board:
H1, H2, H3: MountingHole_2.7mm_M2.5

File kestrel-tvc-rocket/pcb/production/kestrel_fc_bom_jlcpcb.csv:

Comment,Designator,Footprint,LCSC Part #
TMB12A03,BZ1,Buzzer_12x9.5RM7.6,C96222
10uF,"C1,C6,C11,C14,C15,C21,C25",C_0805_2012Metric,C15850
100nF,"C2,C3,C4,C5,C10,C16,C17,C18,C19,C20,C22,C24",C_0402_1005Metric,C1525
22uF,"C7,C8,C9,C12,C13",C_1206_3216Metric,C12891
47pF,C23,C_0402_1005Metric,C1567
SMF13A,D1,D_SOD-123F,C41376087
B5819W,D2,D_SOD-123,C8598
1N5819WS,D3,D_SOD-323,C191023
GREEN,D4,LED_0805_2012Metric,C2297
RED,D5,LED_0805_2012Metric,C84256
600R@100MHz,FB1,L_0805_2012Metric,C1017
BATT 2S (balance plug),J1,JST_XH_B3B-XH-A_1x03_P2.50mm_Vertical,C144394
SERVO1 TVC RING,J2,PinHeader_1x03_P2.54mm_Vertical,C49257
SERVO2 TVC MOTOR,J3,PinHeader_1x03_P2.54mm_Vertical,C49257
SERVO3 RELEASE,J4,PinHeader_1x03_P2.54mm_Vertical,C49257
SERVO4 TAB1,J5,PinHeader_1x03_P2.54mm_Vertical,C49257
"RADIO (SiK, Pixhawk TELEM)",J7,JST_GH_BM06B-GHS-TBT_1x06-1MP_P1.25mm_Vertical,C189892
GPS ANT (U.FL),J8,U.FL_Hirose_U.FL-R-SMT-1_Vertical,C88374
Pico2W pins 1-20,J10,PinSocket_1x20_P2.54mm_Vertical,C7499336
Pico2W pins 21-40,J11,PinSocket_1x20_P2.54mm_Vertical,C7499336
SERVO5 TAB2,J12,PinHeader_1x03_P2.54mm_Vertical,C49257
SERVO6 TAB3,J13,PinHeader_1x03_P2.54mm_Vertical,C49257
SERVO7 TAB4,J14,PinHeader_1x03_P2.54mm_Vertical,C49257
3.3uH,"L1,L2",L_Sunlord_MWSA0503S,C408409
15nH,L3,L_0402_1005Metric,C27143
AO3401A,"Q1,Q2",SOT-23,C15127
2N7002,Q3,SOT-23,C8545
AO3400A,Q4,SOT-23,C20917
100k,"R1,R3,R5,R12,R13,R14,R15,R19,R32",R_0402_1005Metric,C25741
47k,"R2,R4",R_0402_1005Metric,C25792
33k,"R6,R9,R16",R_0402_1005Metric,C25779
1M,"R7,R8",R_0402_1005Metric,C26083
22k,"R10,R17",R_0402_1005Metric,C25768
10k,"R11,R18,R20,R21,R22",R_0402_1005Metric,C25744
0,R23,R_0402_1005Metric,C17168
220,"R25,R26,R27,R28,R37,R38,R39",R_0402_1005Metric,C25091
100,R31,R_0402_1005Metric,C25076
120,R33,R_0402_1005Metric,C25079
330,R34,R_0402_1005Metric,C25104
POWER,SW1,SW_SPDT_PCM12,C221841
USER,SW2,SW_Push_1P1T_XKB_TS-1187A,C318884
RESET,SW3,SW_Push_1P1T_XKB_TS-1187A,C318884
TPS563201,"U2,U3",TSOT-23-6,C116592
LSM6DSO,U4,LGA-14_3x2.5mm_P0.5mm_LayoutBorder3x4y,C2655100
BMP580,U5,Bosch_LGA-10_2x2mm_P0.5mm_BMP58x,C22391138
W25Q128JVSIQ,U6,SOIC-8_5.23x5.23mm_P1.27mm,C97521
ATGM336H-5N31,U7,ublox_MAX,C90770

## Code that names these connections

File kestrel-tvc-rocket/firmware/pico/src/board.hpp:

// KESTREL FC v3.0 - Raspberry Pi Pico 2 W pin map (source of truth: pcb/circuit.py)
#pragma once
#include "pico/types.h"

namespace board {

constexpr uint GPS_TX = 0;          // UART0 TX -> ATGM336H RXD
constexpr uint GPS_RX = 1;          // UART0 RX <- ATGM336H TXD
constexpr uint SERVO_PWR_OFF = 3;   // high = servo 5 V buck OFF (board pull-down keeps it ON by default)
constexpr uint RADIO_TX = 4;        // UART1 TX -> radio socket J7 pin 2 (telemetry radio RX)   (v2 boards: Qwiic SDA)
constexpr uint RADIO_RX = 5;        // UART1 RX <- radio socket J7 pin 3 (telemetry radio TX)   (v2 boards: Qwiic SCL)
// Servo ports 1-7 (PWM slices 3A 3B 4A 4B 1A 6B 7B, all 50 Hz):
//   1 TVC ring, 2 TVC motor holder, 3 parachute release latch, 4-7 fin tabs 1-4 (fins at 45/135/225/315 deg)
constexpr int SERVO_COUNT = 7;
constexpr uint SERVO_PWM[SERVO_COUNT] = {6, 7, 8, 9, 2, 13, 15};
constexpr uint BUZZER = 10;         // high = on (active 3 V buzzer via AO3400A)
constexpr uint LED_GREEN = 11;      // high = on
constexpr uint LED_RED = 12;        // high = on
constexpr uint BUTTON = 14;         // USER button to GND (internal pull-up)
constexpr uint SPI_MISO = 16;       // SPI0 RX
constexpr uint CS_IMU = 17;         // LSM6DSO
constexpr uint SPI_SCK = 18;
constexpr uint SPI_MOSI = 19;       // SPI0 TX
constexpr uint CS_BARO = 20;        // BMP580
constexpr uint CS_FLASH = 21;       // W25Q128JV (16 MB flight log)
constexpr uint BARO_INT = 22;
constexpr uint ADC_VBAT = 26;       // ADC0: switched battery via 100k/33k
constexpr uint ADC_CELL1 = 27;      // ADC1: cell-1 tap via 1M/1M
constexpr uint ADC_SERVO_V = 28;    // ADC2: servo 5 V rail via 100k/100k

constexpr float VBAT_DIV = (100.0f + 33.0f) / 33.0f;
constexpr float CELL1_DIV = 2.0f;
constexpr float SERVO_V_DIV = 2.0f;
constexpr float ADC_VREF = 3.30f;

constexpr unsigned LOOP_HZ = 500;   // flight-core rate (matches the simulator / SIL tests)
constexpr unsigned SPI_HZ = 8000000;

}  // namespace board
